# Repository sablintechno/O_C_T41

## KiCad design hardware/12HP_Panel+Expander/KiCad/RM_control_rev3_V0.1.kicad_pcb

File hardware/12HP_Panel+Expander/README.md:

<h1>Front PCB</h1>

<h1>Front</h1>

<h1>Side</h1>

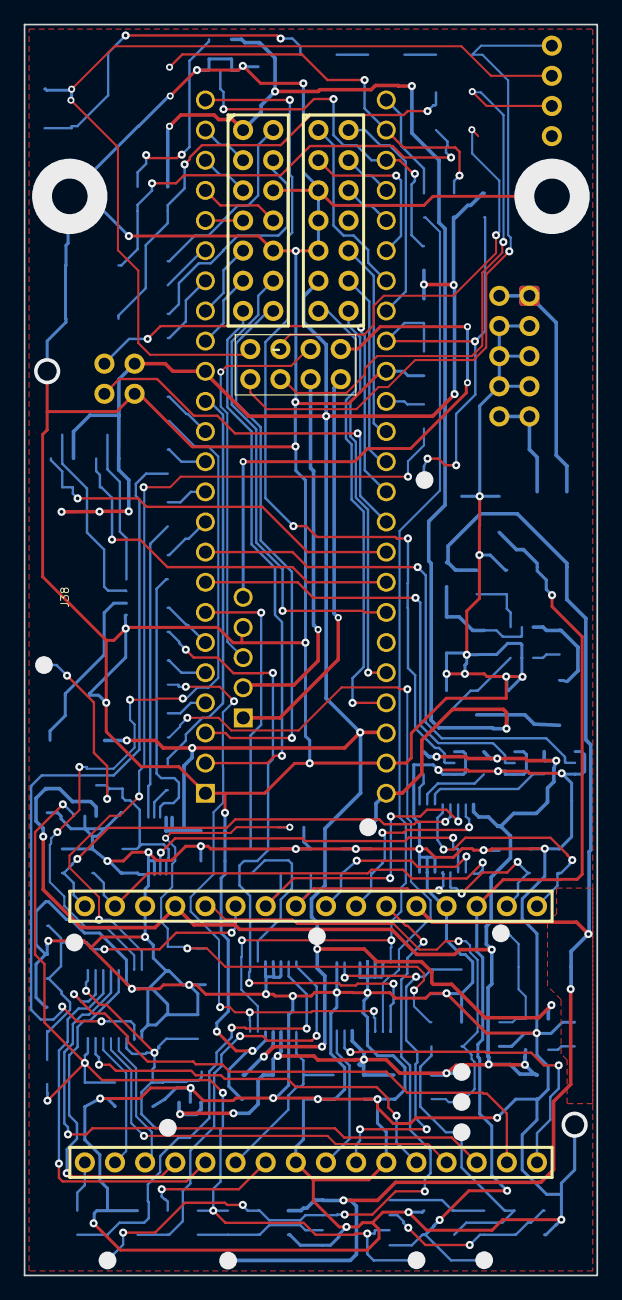
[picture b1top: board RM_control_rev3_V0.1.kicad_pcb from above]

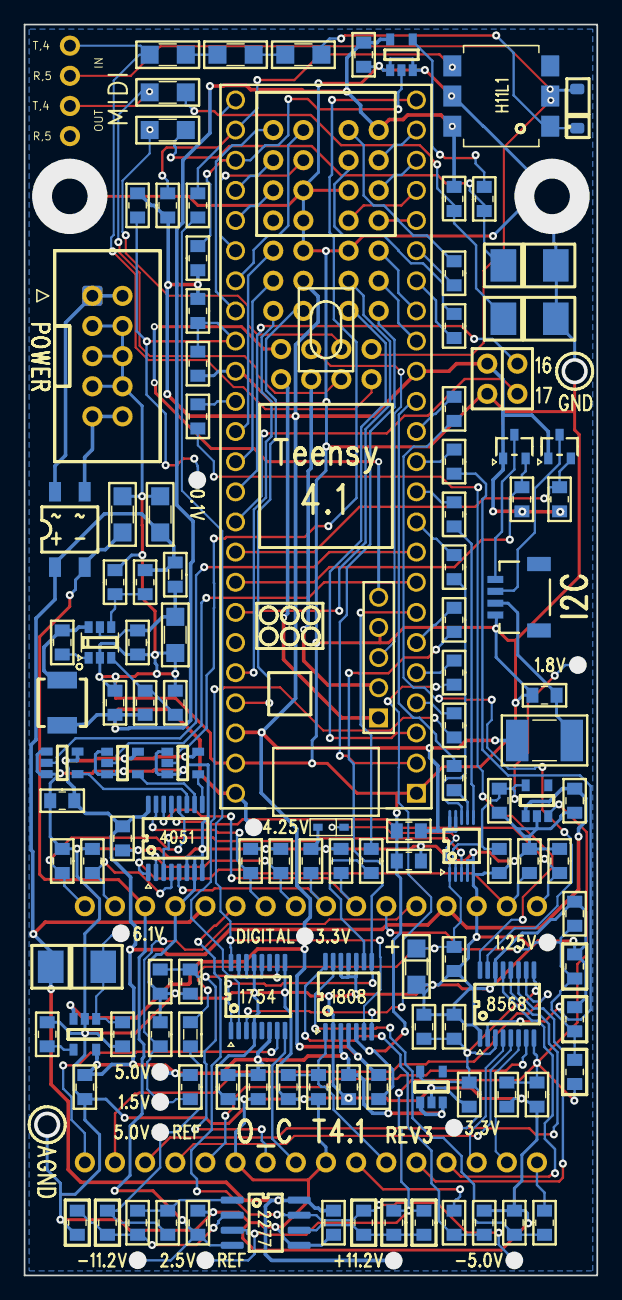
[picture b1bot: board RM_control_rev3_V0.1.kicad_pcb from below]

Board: 2 copper layers, 48.3 x 105.4 mm, 128 parts (2 on the bottom side), 126 nets.

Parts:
C52, C54, C57, C60, C61, C71, C73, C74, C81, C82, C83, C84, C85, C86, C87, C88, C89, C90, C91, C92: C_0805_2012METRIC_PAD1.18X1.45MM_HANDSOLDER_RECTP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; C_0805_2012Metric_Pad1.18x1.45mm_HandSolder_rectpads
C53, C55, C56, C58, C59, C62, C63, C64, C65, C66, C67, C68, C69, C70, C72, C75, C76, C77, C78, C79, C80, C94: C_0805_2012METRIC_PAD1.18X1.45MM_HANDSOLDER_RECTP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; C_0805_2012Metric_Pad1.18x1.45mm_HandSolder_rectpads_C53
C93, C97: C_1206_3216METRIC_PAD1.33X1.80MM_HANDSOLDER_RECTP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; C_1206_3216Metric_Pad1.33x1.80mm_HandSolder_rectpads
C95, C96: C_1206_3216METRIC_PAD1.33X1.80MM_HANDSOLDER_RECTP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; C_1206_3216Metric_Pad1.33x1.80mm_HandSolder_rectpads_C95
D1: DIODE_BRIDGE_REDUCED; Diode_Bridge_reduced
D2, D3, D4: D_SMB_HANDSOLDERING_RECTPADS; D_SMB_Handsoldering_rectpads
D5: D_SOD-123
D6: D_SOD-323F_RECTPADS; D_SOD-323F_rectpads
F1: FUSE_1812_4532METRIC_PAD1.30X3.40MM_HANDSOLDER_RE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; Fuse_1812_4532Metric_Pad1.30x3.40mm_HandSolder_rectpads
J1: PINSOCKET_1X04_P2.54MM_VERTICAL_REDUCED; PinSocket_1x04_P2.54mm_Vertical_reduced
J28, J29: PINSOCKET_2X07_P2.54MM_VERTICAL_REDUCED; PinSocket_2x07_P2.54mm_Vertical_reduced
J30, J31: PINSOCKET_1X16_P2.54MM_VERTICAL_REDUCED; PinSocket_1x16_P2.54mm_Vertical_reduced
J32: IDC-HEADER_2X05_P2.54MM_VERTICAL_REDUCED; IDC-Header_2x05_P2.54mm_Vertical_reduced
J33: PINSOCKET_2X04_P2.54MM_VERTICAL_REDUCED; PinSocket_2x04_P2.54mm_Vertical_reduced
J34: PINHEADER_2X02_P2.54MM_VERTICAL_SYMMETRIC; PinHeader_2x02_P2.54mm_Vertical_symmetric
J38: JST_SMD_1.0MM-4; JST_SMD_1.0mm-4
L1: L_0805_2012METRIC_RECTPADS; L_0805_2012Metric_rectpads
L2: L_ABRACON_ASPI-4030S_RECTPADS; L_Abracon_ASPI-4030S_rectpads
L3: L_0805_2012METRIC_RECTPADS; L_0805_2012Metric_rectpads_L3
Q1, Q2: SOT-23-3_RECTPADS; SOT-23-3_rectpads
R103, R104, R112, R119, R120, R122, R123, R124, R126, R127, R128, R131, R132, R133, R134, R136, R137, R138, R144, R200: R_0805_2012METRIC_PAD1.20X1.40MM_HANDSOLDER_RECTP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; R_0805_2012Metric_Pad1.20x1.40mm_HandSolder_rectpads
R105, R106, R107, R108, R109, R110, R111, R113, R114, R115, R116, R117, R118, R121, R125, R129, R130, R135, R201, R202: R_0805_2012METRIC_PAD1.20X1.40MM_HANDSOLDER_RECTP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; R_0805_2012Metric_Pad1.20x1.40mm_HandSolder_rectpads_R105
R139, R140, R141, R142, R143: R_1206_3216METRIC_PAD1.30X1.75MM_HANDSOLDER_RECTP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; R_1206_3216Metric_Pad1.30x1.75mm_HandSolder_rectpads
U12: TEENSY41; Teensy41
U13: SOT-23-6_RECTPADS; SOT-23-6_rectpads
U14: SOT-23-5_REDUCEDPADS; SOT-23-5_reducedpads
U15, U16, U20, U21, U22, U23: SOT-23-5_REDUCEDPADS; SOT-23-5_reducedpads_U15
U17: MSOP-10_3X3MM_P0.5MM_SILKSCREEN+FOOTPRINT; MSOP-10_3x3mm_P0.5mm_silkscreen+footprint
U18, U19, U25: TSSOP-16_4.4X5MM_P0.65MM_SILKSCREEN; TSSOP-16_4.4x5mm_P0.65mm_silkscreen
U24: TSSOP-14_4.4X5MM_P0.65MM_SILKSCREEN; TSSOP-14_4.4x5mm_P0.65mm_silkscreen
U26: SOIC-8_3.9X4.9MM_P1.27MM_SHIFTEDPADS; SOIC-8_3.9x4.9mm_P1.27mm_shiftedpads
U27: OPTOCOUPLER_H11F3SR2M

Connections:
+3v3: C57.1, C63.1, F1.2, J28.12, J34.1, Q1.1, Q2.1, R119.1, R120.1, R122.1, R123.1, R130.1, R202.1, U12.3.3V, U12.3.3V@, U14.3, U17.9, U17.10, U24.4
+4v: C74.1, C94.1, J29.2, L2.2, R116.1, R127.1, U12.VIN, U23.5, U27.6
+5va: C54.1, C55.1, C64.1, C66.1, C70.1, C72.1, C76.1, J30.4, R125.1, U14.5, U15.1, U15.3, U16.1, U18.16, U20.5, U21.5, U22.5, U24.3, U25.6
+12va: C67.1, C95.1, D1.1, D2.1, J30.12, L1.1, R129.1, U26.8
-12va: C68.2, C96.1, D1.2, J30.14, U26.4
/adc_cs: R107.1, U12.9
/adc_miso: R112.2, U12.12
/adc_mux_a0: U12.7, U20.2
/adc_mux_a1: U12.6, U21.2
/adc_mux_a2: U12.32, U22.2
/adc_sck: R108.1, U12.8
/dac_cs: R106.1, U12.10
/dac_mosi: R105.1, U12.11
/dac_sck: R114.1, U12.13
/debug1: J34.2, U12.16
/debug2: J34.4, U12.17
/enc_l_a: J29.4, U12.31
/enc_l_b: J29.6, U12.30
/enc_l_sw: J29.12, U12.24
/enc_r_a: J28.5, U12.37
/enc_r_b: J28.3, U12.36
/enc_r_sw: J29.10, U12.25
/hw_id: R121.1, R130.2, R202.2, U12.41
/i2c_scl: Q1.2, R122.2, U12.19
/i2c_sda: Q2.2, R123.2, U12.18
/i2s_bclk: R109.1, U12.4
/i2s_data_adc: R113.1, U12.5
/i2s_data_dac: R111.1, U12.2
/i2s_lrclk: R110.1, U12.3
/i2s_mclk: R115.1, U12.33
/midi_in: R119.2, U12.34, U27.4
/midi_out: R120.2, U12.35, U23.2
/oled_cs: J28.1, U12.40
/oled_dc: J28.2, U12.39
/oled_mosi: R104.1, U12.26
/oled_rst: J28.4, U12.38
/oled_sck: R103.1, U12.27
/sw_a: J29.7, U12.29
/sw_b: J28.9, U12.14
/sw_x: J29.8, U12.28
/sw_y: J28.11, U12.15
/sw_zap: J29.11, U12.20
/tr1: J29.14, U12.0
/tr2: J29.13, U12.1
/tr3: J28.14, U12.23
/tr4: J28.13, U12.22
D+_B: J33.6, U12.D+
D-_B: J33.5, U12.D-
SHLD_B: J33.8, U12.GND@_3
VBUS_B: J33.7, U12.+5V
earth: C53.2, C57.2, C63.2, C73.2, C74.2, C94.2, C95.2, C96.2, C97.2, D3.2, D4.2, J28.6, J28.8, J28.10, J29.5, J29.9, J32.3, J32.4, J32.5, J32.6, J32.7, J32.8, J34.3, J38.1, R121.2, R126.2, R128.2, R144.1, U12.GND, U12.GND@, U12.GND@_1, U12.GND@_2, U13.2, U23.1, U23.3, U24.5, U27.5
gnd: C54.2, C55.2, C56.2, C58.2, C59.2, C60.2, C61.2, C62.2, C64.2, C65.2, C66.2, C67.2, C68.1, C69.2, C70.2, C71.2, C72.2, C75.2, C76.2, C77.2, C78.2, C79.2, C80.2, C81.2, C82.2, C83.2, C84.2, C85.2, C86.2, C87.2, C88.2, C89.2, C90.2, C91.2, C93.2, D6.2, J30.3, J30.13, J31.8, J31.11, R124.2, R133.2, R136.1, R144.2, R200.2, U14.2, U15.2, U16.2, U17.4, U17.5, U18.6, U18.7, U18.8, U19.1, U19.14, U20.1, U20.3, U21.1, U21.3, U22.1, U22.3, U24.2, U24.10, U24.11, U24.12, U25.4, U25.9, U25.12, U25.13, U25.14, U25.15, U26.5
net-(c92-pad2): C92.2, R118.1, U26.1
net-(d2-a): C69.1, D2.2, U14.1
net-(d3-k): D3.1, R117.2, R140.1
net-(d4-k): D4.1, R116.2, R139.1
net-(d5-a): D5.2, J1.2, J33.2, U27.2
net-(d5-k): D5.1, R141.1, U27.1
net-(d6-k): C59.1, C93.1, D6.1, L3.2, U17.1
net-(j29-pin_1): J29.1, R103.2
net-(j29-pin_3): J29.3, R104.2
net-(j30-pin_1): C88.1, J30.1, U18.13
net-(j30-pin_2): C87.1, J30.2, U18.1
net-(j30-pin_5): J30.5, R124.1, R125.2
net-(j30-pin_6): C61.1, J30.6, R133.1, R134.2, R200.1
net-(j30-pin_7): C86.1, J30.7, U18.14
net-(j30-pin_8): C85.1, J30.8, U18.5
net-(j30-pin_9): C84.1, J30.9, U18.2
net-(j30-pin_10): C83.1, J30.10, U18.15
net-(j30-pin_11): J30.11, R138.2, U26.7
net-(j30-pin_15): C82.1, J30.15, U18.4
net-(j30-pin_16): C81.1, J30.16, U18.12
net-(j31-pin_1): J31.1, R132.2
net-(j31-pin_2): J31.2, U19.6
net-(j31-pin_3): J31.3, U19.4
net-(j31-pin_4): J31.4, U19.13
net-(j31-pin_5): J31.5, U19.11
net-(j31-pin_6): C65.1, C77.1, J31.6, U24.1
net-(j31-pin_7): J31.7, R131.2
net-(j31-pin_9): J31.9, U25.8
net-(j31-pin_10): C56.1, C75.1, J31.10, U25.10
net-(j31-pin_12): J31.12, U19.7
net-(j31-pin_13): J31.13, U19.5
net-(j31-pin_14): J31.14, U19.12
net-(j31-pin_15): J31.15, U19.10
net-(j31-pin_16): J31.16, U25.7
net-(j32-pin_1): D1.3, J32.1, J32.2
net-(j32-pin_10): D1.4, J32.9, J32.10
net-(j33-pin_1): J1.1, J33.1, R143.2
net-(j33-pin_3): J1.3, J33.3, R139.2
net-(j33-pin_4): J1.4, J33.4, R140.2
net-(j38-pin_2): C73.1, F1.1, J38.2
net-(j38-pin_3): J38.3, Q2.3
net-(j38-pin_4): J38.4, Q1.3
net-(l3-pad1): L3.1, R118.2, R137.2
net-(r141-pad2): R141.2, R142.1
net-(r142-pad2): R142.2, R143.1
net-(u13-cb): C52.1, U13.1
net-(u13-en): R128.1, R129.2, U13.4
net-(u13-fb): R126.1, R127.2, U13.3
net-(u13-sw): C52.2, L2.1, U13.6
net-(u13-vin): C53.1, C97.1, L1.2, U13.5
net-(u14-bp): C91.1, U14.4
net-(u15-out): C60.1, C71.1, C78.1, U15.5, U19.3, U19.9
net-(u16-en): C62.1, C79.1, R134.1, R135.1, R201.1, U16.3, U19.8, U26.3
net-(u16-out): C58.1, C80.1, U16.5, U17.2
net-(u17-ain+): U17.3, U18.3
net-(u17-cnvst): R107.2, U17.6
net-(u17-sclk): R108.2, U17.8
net-(u17-sdo): R112.1, U17.7
net-(u18-s0): U18.11, U20.4
net-(u18-s1): U18.10, U21.4
net-(u18-s2): U18.9, U22.4
net-(u19-din): R105.2, U19.15
net-(u19-sclk): R114.2, U19.16
net-(u19-~sync): R106.2, U19.2
net-(u23-y): R117.1, U23.4
net-(u24-bck): R109.2, U24.8, U25.1
net-(u24-dout): R113.2, U24.9
net-(u24-lrck): R110.2, U24.7, U25.3
net-(u24-scki): R115.2, U24.6, U25.16
net-(u24-vinl): C90.1, R132.1, U24.13
net-(u24-vinr): C89.1, R131.1, U24.14
net-(u25-data): R111.2, U25.2
net-(u26a--): C92.1, R136.2, R137.1, U26.2
net-(u26b--): R135.2, R138.1, R201.2, U26.6

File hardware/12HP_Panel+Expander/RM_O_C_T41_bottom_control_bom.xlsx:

Comment | Designator | Footprint | LCSC Part # |  |  | Original Part
22pF | C92 | 0805 | C1804 | CL21C220JBANNNC | C105623 | CC0805JRNPO9BN220
 | C81, C82, C83, C84, C85, C86, C87, C88, C89, C90 | 0805 | C1835 | 0805CG681J500NT | C107121 | CC0805JRNPO9BN681
10nF | C91 | 0805 | C24666 | 0805B103J500NT | C58456 | CC0805JRX7R9BB103
1.0uF | C69, C70, C71, C72, C73 | 0805 | C541528 | CC0805JKX7R9BB105 | C541528 | CC0805JKX7R9BB105
0.1uF | C52, C53, C54, C55, C56, C57, C58, C59, C60, C61, C62, C63, C64, C65, C66, C67,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 | 0805 | C29926 | 0805B104J500NT | C111492 | CC0805JRX7R9BB104
10uF | C74, C75, C76, C77, C78, C79, C80 | 0805 | C15850 | CL21A106KAYNNNE | C307520 | CL21A106KOQNNNG
10uF | C93 | 1206 | C7171 | TAJA106K016RNJ | C7171 | TAJA106K016RNJ
22uF | C95, C96, C97 | 1206 | C12891 | CL31A226KAHNNNE | C12891 | CL31A226KAHNNNE
Bridge Rectifier | D1 | TO-269AA | C52151 | HD01-T | C52151 | HD01-T
Diode Zener | D2, D3, D4 |  | C142361 | 1SMB5918BT3G | C142361 | 1SMB5918BT3G
Diode | D5 | SDO123 | C77978 | 1N4148W-TP | C77978 | 1N4148W-TP
Diode | D6 | SDO123 |  |  |  | BZT52B5V1S | mod 5V
PTC Fuse | F1 | 1812 | C12430 | MF-MSMF010-2 | C12430 | MF-MSMF010-2
Ferrite Bead | L1 | 0805 | C2441364 | HZ0805E601R-10 | C2441364 | HZ0805E601R-10
Inductor | L2 |  | C2921170 | BCIHP0420SC-100M | C2921170 | BCIHP0420SC-100M | LQH44NN100K03L | LQH44PH100MPRL | CY43-10UH | MDA4020-100M | IFSC1515AHER100M01
Inductor | L3 | 0805 | C223145 | BRC2012T1R5MD | C223145 | BRC2012T1R5MD
Mosfet | Q1, Q2 | SOT23 | C80498 | FDV303N | C80498 | FDV303N
0 | R144 | 0805 | C17477 | 0805W8F0000T5E | C17477 | 0805W8F0000T5E
75 | R141, R142, R143 | 1206 | C17987 | 1206W4F750JT5E | C4185489 | CRCW120675R0FKEAC
120 | R139, R140 | 1206 |  |  |  |  | mod 5V
100 | R103, R104, R105, R106, R107, R108, R109, R110, R111, R112, R113, R114, R115, R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 | 0805 | C17408 | 0805W8F1000T5E | C105577 | RC0805FR-07100RL
220 | R118 | 0805 | C17557 | 0805W8F2200T5E | C114519 | RC0805FR-07220RL
470 | R119 | 0805 | C17710 | 0805W8F4700T5E | C114564 | RC0805FR-07470RL
1K | R131, R132 | 0603 | C21190 | 0603WAF1001T5E | C22548 | RC0603FR-071KL
5.11K 1% | R126 | 0805 | C46039 | 0805W8F5111T5E | C276311 | RC0805FR-075K11L
10K 0,005% | R133, R134, R135, R136, R137 | 0805 | C706400 | RT0805WRD0710KL | C2073470 | ERA-6ARW103V
4k7 | R133 | 0805 |  |  |  |  | mod DAC
5k8 | R134 | 0805 |  |  |  |  | mod DAC
4.7K 1% | R121, R123, R124, R120, R122 | 0805 | C17673 | 0805W8F4701T5E | C60816 | RC0805FR-074K7L
11K | R125 | 0805 | C17429 | 0805W8F1102T5E | C137597 | RC0805FR-0711KL
20K 0,05% | R138 | 0805 | C706402 | RT0805WRD0720KL | C4141407 | ERA-6ARW203V | AR05ATB2002 | PTFR0805Q20K0N9
22K | R128 | 0805 | C17560 | 0805W8F2202T5E | C114565 | RC0805FR-0722KL
27k | R127 | 0805 |  |  |  |  | mod 5V
150K 1% | R129 | 0805 | C17470 | 0805W8F1503T5E | C114558 | RC0805FR-07150KL
100K 1% | R130 | 0805 |  |  |  |  | mod HW
DNP | R200, R201, R202
Buck Converter | U13 | SOT-23-6 | C3193129 | LMR54406FDBVR | C3193129 | LMR54406FDBVR
LDO 5V | U14 | SOT-23-5 | C37560592 | LP2985A-50DBVRM3 | C37560592 | LP2985A-50DBVRM3 | LP2985-50DBVR
LDO 3.3V | U15 | SOT-23-5 | C2862740 | TPS7A2033PDBVR | C2862740 | TPS7A2033PDBVR
LDO 1.8V | U16 | SOT-23-5 | C92498 | LP5907MFX-1.8/NOPB | C92498 | LP5907MFX-1.8/NOPB
ADC | U17 | MSOP-10 | C635977 | MCP33131D-05-E/MS | C635977 | MCP33131D-05-E/MS
analog mux | U18 | TSSOP-16 | C547982 | 74LV4051PW,118 | C547982 | 74LV4051PW,118
DAC | U19 | TSSOP-16 | C2680013 | DAC8568IBPWR | C2680013 | DAC8568IBPWR
Buffer level shifter | U20, U21, U22, U23 | SOT-23-5 | C473338 | SN74LV1T125DBVR | C473338 | SN74LV1T125DBVR
Audio ADC | U24 | TSSOP-14 | C55513 | PCM1808PWR | C55513 | PCM1808PWR
Audio DAC | U25 | SSOP-16-150mil | C294211 | PCM1754DBQR | C294211 | PCM1754DBQR
Dual Opamp | U26 | SOIC-8 | C962986 | OPA2277UA | C962986 | OPA2277UA
Optocoupler | U27 | DIP6 | C78588 | H11L1 | C78588 | H11L1 | H11L1SVM
J38 | 1 | Connector, JST 4 pin, Sparkfun QWIIC |  |  |  | PRT-14417
J28-J29 | 2 | Socket, 7x2 (omit if soldering boards together) |  |  |  | TSW-107-06-T-S
J30-J31 | 2 | Socket, 16x1 (omit if soldering boards together) |  |  |  | TSW-116-06-T-S
J32 | 1 | Header, 5x2 Shrouded |  |  |  | 68015-405HLF
J33 | 1 | Header, 4x1 |  |  |  | 68000-204HLF
J34-J35 | 2 | Header, 2x1 (omit if debug signals not needed)
J36-J37 | 2 | Test Point (omit if not needed) Keystone 5011
U12 | 1 | Teensy 4.1 (with headers and sockets) |  |  |  | 16996

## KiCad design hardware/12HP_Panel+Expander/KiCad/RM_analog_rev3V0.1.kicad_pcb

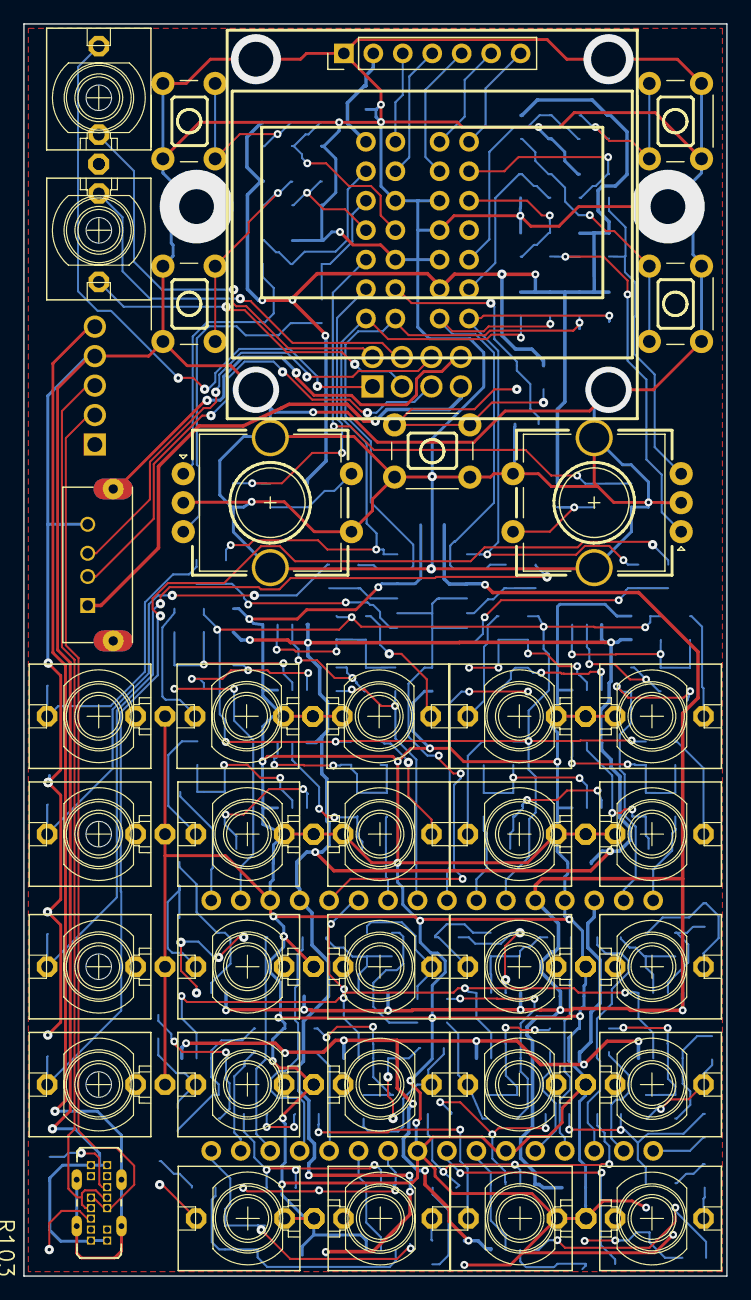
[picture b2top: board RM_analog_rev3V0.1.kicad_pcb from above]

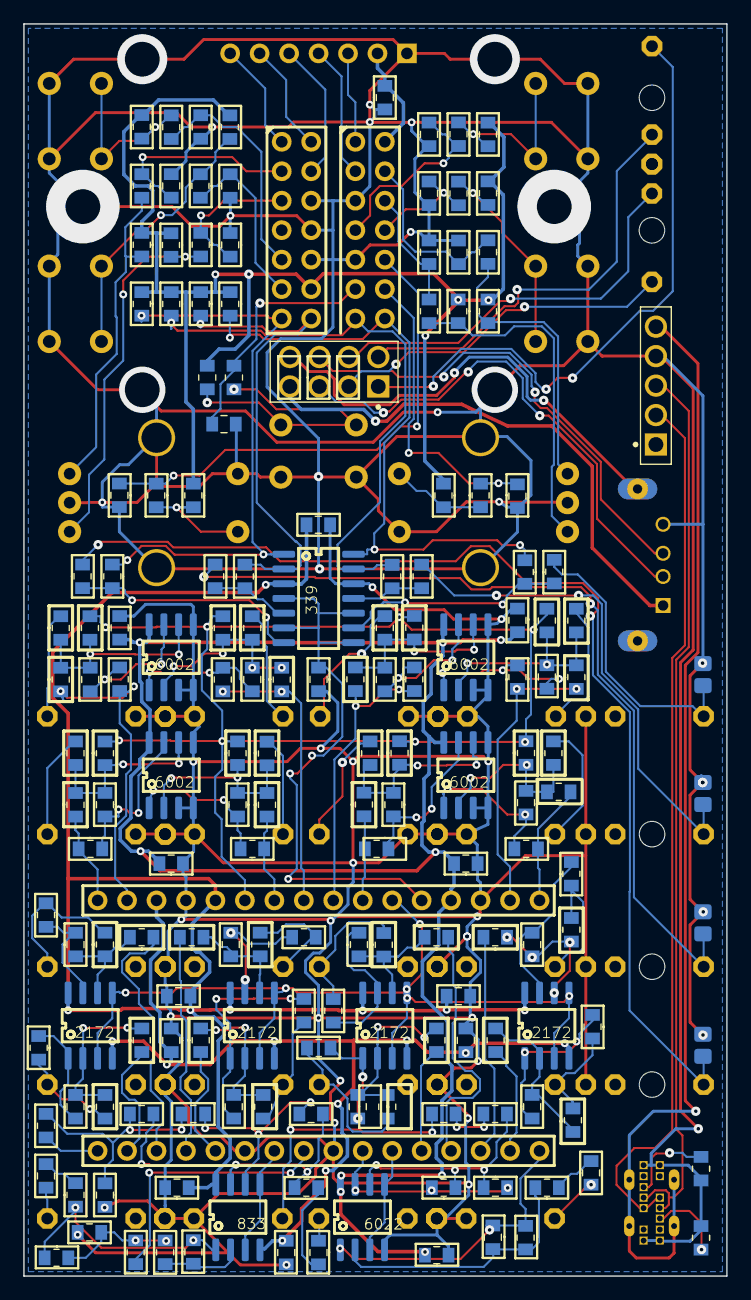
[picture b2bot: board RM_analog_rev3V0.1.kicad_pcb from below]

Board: 2 copper layers, 60.6 x 108.0 mm, 212 parts (6 on the bottom side), 148 nets.

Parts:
C1, C2, C3, C4, C5, C11, C12, C26, C28, C30, C34, C35, C36, C37, C48, C50: C_0805_2012METRIC_PAD1.18X1.45MM_HANDSOLDER_RECTP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; C_0805_2012Metric_Pad1.18x1.45mm_HandSolder_rectpads
C6, C7, C8, C9, C10, C13, C14, C15, C16, C17, C18, C19, C20, C21, C22, C23, C24, C25, C27, C29, C31, C32, C33, C38, C39, C40, C41, C42, C43, C44, C45, C46, C47, C49, C51: C_0805_2012METRIC_PAD1.18X1.45MM_HANDSOLDER_RECTP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; C_0805_2012Metric_Pad1.18x1.45mm_HandSolder_rectpads_C6
J1: DEV_J1; P51
J2: DEV_J2; P51
J3: DEV_J3; P51
J4, J8: JACK O_C; Jack_O_C
J5: DEV_J5; P51
J6: DEV_J6; P51
J7: DEV_J7; P51
J9: DEV_J9; P51
J10: DEV_J10; P51
J11: DEV_J11; P51
J12: DEV_J12; P51
J13: DEV_J13; P51
J14: DEV_J14; P51
J15: DEV_J15; P51
J16: DEV_J16; P51
J17: DEV_J17; P51
J18: DEV_J18; P51
J19: DEV_J19; P51
J20: DEV_J20; P51
J21: PINHEADER_1X07_P2.54MM_VERTICAL; PinHeader_1x07_P2.54mm_Vertical
J22, J23: PINHEADER_2X07_P2.54MM_VERTICAL_REDUCED; PinHeader_2x07_P2.54mm_Vertical_reduced
J24: RHDRV8W80P254_4X2_1066X508H865_AP1
J25: RHDRV5W80P254_5X1_1320X250H875_AP1
J26, J27: PINHEADER_1X16_P2.54MM_VERTICAL_REDUCED; PinHeader_1x16_P2.54mm_Vertical_reduced
MIDI_IN0: DEV_MIDI_IN; P78
MIDI_OUT0: DEV_MIDI_OUT; P78
R1, R2, R3, R4, R5, R10, R11, R12, R13, R14, R15, R16, R23, R24, R25, R26, R27, R28, R29, R30, R35, R36, R37, R38, R39, R40, R41, R42, R51, R52, R53, R54, R55, R56, R57, R58, R59, R60, R61, R62, R79, R80, R81, R82, R83, R87, R89, R90, R101: R_0805_2012METRIC_PAD1.20X1.40MM_HANDSOLDER_RECTP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; R_0805_2012Metric_Pad1.20x1.40mm_HandSolder_rectpads
R6, R7, R8, R9, R17, R18, R19, R20, R21, R22, R31, R32, R33, R34, R43, R44, R45, R46, R47, R48, R49, R50, R63, R64, R65, R66, R67, R68, R69, R70, R71, R72, R73, R74, R75, R76, R77, R78, R84, R85, R86, R88, R91, R92, R93, R94, R95, R96, R97, R98, R99, R100, R102: R_0805_2012METRIC_PAD1.20X1.40MM_HANDSOLDER_RECTP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; R_0805_2012Metric_Pad1.20x1.40mm_HandSolder_rectpads_R6
R103: 4k7; R_0805_2012Metric_Pad1.20x1.40mm_HandSolder_rectpads_R103
R104: 4k7; R_0805_2012Metric_Pad1.20x1.40mm_HandSolder_rectpads_R104
R105, R106, R107, R108: 100K; RES_0805
SW1, SW2, SW3, SW4, SW5: SW_PUSH_6MM; SW_PUSH_6mm
SW6, SW7: ROTARYENCODER_ALPS_EC11E-SWITCH_VERTICAL_H20MM_CI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; RotaryEncoder_Alps_EC11E-Switch_Vertical_H20mm_CircularMoun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
TR1: DEV_TR1; P51
TR2: DEV_TR2; P78
TR3: DEV_TR3; P78
TR4: DEV_TR4; P78
U1: SOIC-14_3.9X8.7MM_P1.27MM_SHIFTEDPADS; SOIC-14_3.9x8.7mm_P1.27mm_shiftedpads
U2, U3, U4, U5, U6, U7, U8, U9, U10, U11: SOIC-8_3.9X4.9MM_P1.27MM_SHIFTEDPADS; SOIC-8_3.9x4.9mm_P1.27mm_shiftedpads
USB_A0: USB_A_ALIEXPRESS_VERTICAL; USB_A_AliExpress_Vertical
USB_C0: SPARKFUN USB-C VERTICAL; SparkFun_USB-C_Vertical

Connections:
+3v3: J23.12, R1.1, R2.1, R3.1, R4.1, R5.1, R11.1, R12.1, R13.1, R14.1, R15.1, R16.1, R23.1, R24.1, R25.1, R26.1
+5va: C14.1, C15.1, C16.1, C17.1, C31.1, J26.4, U2.8, U3.8, U4.8, U5.8, U10.8
+12va: C13.1, C27.1, C29.1, C32.1, J26.12, U1.3, U6.8, U7.8, U8.8, U9.8, U11.8
-12va: C28.2, C30.2, C33.2, J26.14, U6.4, U7.4, U8.4, U9.4, U11.4
/audio_in_l: C46.1, J27.1, R101.2, U10.1
/audio_in_r: C47.1, J27.7, R102.2, U10.7
/audio_out_l: J27.16, R93.1
/audio_out_r: J27.9, R94.1
/bias: J26.6, U6.3, U6.5, U7.3, U7.5, U8.3, U8.5, U9.3, U9.5
/clk: J21.3, J22.1
/cs: J21.7, J23.1
/cv1: J26.2, R51.2, R59.2
/cv2: J26.8, R52.2, R60.2
/cv3: J26.9, R53.2, R61.2
/cv4: J26.15, R54.2, R62.2
/cv5: J26.1, R55.2, R63.2
/cv6: J26.7, R56.2, R64.2
/cv7: J26.10, R57.2, R65.2
/cv8: J26.16, R58.2, R66.2
/cv_a: J27.3, R67.1
/cv_b: J27.4, R68.1
/cv_c: J27.13, R69.1
/cv_d: J27.14, R70.1
/cv_e: J27.2, R71.1
/cv_f: J27.5, R72.1
/cv_g: J27.12, R73.1
/cv_h: J27.15, R74.1
/dac_a: J9.T, R75.2, R83.2
/dac_b: J10.T, R76.2, R84.2
/dac_c: J11.T, R77.2, R85.2
/dac_d: J12.T, R78.2, R86.2
/dac_e: J13.T, R79.2, R87.2
/dac_f: J14.T, R80.2, R88.2
/dac_g: J15.T, R81.2, R89.2
/dac_h: J16.T, R82.2, R90.2
/dc: J21.6, J23.2
/offset: J26.11, R43.2, R44.2, R45.2, R46.2, R47.2, R48.2, R49.2, R50.2
/res: J21.5, J23.4
/sda: J21.4, J22.3
/thres: C26.1, J26.5, U1.4, U1.6, U1.8, U1.10
/tr1: J22.14, R23.2, R31.2, U1.14
/tr2: J22.13, R24.2, R32.2, U1.13
/tr3: J23.14, R25.2, R33.2, U1.2
/tr4: J23.13, R26.2, R34.2, U1.1
/vcc: C1.1, J21.2, J22.2
D+_B: J24.6, USB_A0.3
D+_C: J25.3, USB_C0.A6, USB_C0.B6
D-_B: J24.5, USB_A0.2
D-_C: J25.2, USB_C0.A7, USB_C0.B7
Net_141: R103.2, USB_C0.B5
Net_142: R104.1, USB_C0.A5
SHLD: J25.5, USB_C0.S1, USB_C0.S1@, USB_C0.S1@_1, USB_C0.S1@_2
SHLD_B: J24.8, USB_A0.5, USB_A0.5@
VBUS_B: J24.7, USB_A0.1
earth: C1.2, C2.2, C3.2, C4.2, C5.2, C6.2, C7.2, C8.2, C9.2, C10.2, C11.2, C12.2, J21.1, J22.5, J22.9, J23.6, J23.8, J23.10, J25.4, R103.1, R104.2, R105.2, R106.2, R107.2, R108.2, SW1.1, SW1.1@, SW2.1, SW2.1@, SW3.1, SW3.1@, SW4.1, SW4.1@, SW5.1, SW5.1@, SW6.C, SW6.MP, SW6.MP@, SW6.S2, SW7.C, SW7.MP, SW7.MP@, SW7.S2, USB_A0.4, USB_C0.A1, USB_C0.A12, USB_C0.B1, USB_C0.B12
gnd: C13.2, C14.2, C15.2, C16.2, C17.2, C26.2, C27.2, C28.1, C29.2, C30.1, C31.2, C32.2, C33.1, C42.1, C43.1, J1.S, J1.TN, J2.S, J2.TN, J3.S, J3.TN, J4.S, J4.TN, J5.S, J5.TN, J6.S, J6.TN, J7.S, J7.TN, J8.S, J8.TN, J9.S, J10.S, J11.S, J12.S, J13.S, J14.S, J15.S, J16.S, J17.S, J17.TN, J18.S, J19.S, J19.TN, J20.S, J26.3, J26.13, J27.8, J27.11, TR1.S, TR2.S, TR3.S, TR4.S, U1.12, U2.3, U2.4, U2.5, U3.3, U3.4, U3.5, U4.3, U4.4, U4.5, U5.3, U5.4, U5.5, U10.4
net-(c18-pad1): C18.1, R59.1, U2.1
net-(c19-pad1): C19.1, R60.1, U2.7
net-(c20-pad1): C20.1, R61.1, U3.1
net-(c21-pad1): C21.1, R62.1, U3.7
net-(c22-pad1): C22.1, R63.1, U4.1
net-(c23-pad1): C23.1, R64.1, U4.7
net-(c24-pad1): C24.1, R65.1, U5.1
net-(c25-pad1): C25.1, R66.1, U5.7
net-(c34-pad1): C34.1, R83.1, U6.7
net-(c35-pad1): C35.1, R84.1, U7.7
net-(c36-pad1): C36.1, R85.1, U8.7
net-(c37-pad1): C37.1, R86.1, U9.7
net-(c38-pad1): C38.1, R87.1, U6.1
net-(c39-pad1): C39.1, R88.1, U7.1
net-(c40-pad1): C40.1, R89.1, U8.1
net-(c41-pad1): C41.1, R90.1, U9.1
net-(c42-pad2): C42.2, R93.2, R95.1, R97.2
net-(c43-pad2): C43.2, R94.2, R96.1, R98.2
net-(c44-pad2): C44.2, R91.1, R97.1, U11.7
net-(c45-pad2): C45.2, R92.1, R98.1, U11.1
net-(c48-pad1): C48.1, J18.T
net-(c48-pad2): C48.2, R91.2
net-(c49-pad1): C49.1, J20.T
net-(c49-pad2): C49.2, R92.2
net-(c50-pad1): C50.1, R99.1
net-(c50-pad2): C50.2, J17.T
net-(c51-pad1): C51.1, R100.1
net-(c51-pad2): C51.2, J19.T
net-(d5-a): J24.2, MIDI_IN0.TN
net-(j5-padt): J5.T, R39.1
net-(j6-padt): J6.T, R40.1
net-(j7-padt): J7.T, R41.1
net-(j8-padt): J8.T, R42.1
net-(j22-pin_4): C7.1, J22.4, R17.2
net-(j22-pin_6): C8.1, J22.6, R18.2
net-(j22-pin_7): C2.1, J22.7, R6.1
net-(j22-pin_8): C3.1, J22.8, R7.1
net-(j22-pin_10): C12.1, J22.10, R22.2
net-(j22-pin_11): C6.1, J22.11, R10.1
net-(j22-pin_12): C11.1, J22.12, R21.2
net-(j23-pin_3): C10.1, J23.3, R20.2
net-(j23-pin_5): C9.1, J23.5, R19.2
net-(j23-pin_9): C4.1, J23.9, R8.1
net-(j23-pin_11): C5.1, J23.11, R9.1
net-(j24-pin_1): R27.1, R105.1, TR1.T
net-(j24-pin_3): R28.1, R108.1, TR2.T
net-(j25-pin_1): R29.1, R106.1, TR3.T
net-(j25-pin_3): R30.1, R107.1, TR4.T
net-(j27-pin_6): J27.6, U10.3, U10.5
net-(j27-pin_10): J27.10, U11.3, U11.5
net-(j33-pin_1): J24.1, MIDI_IN0.T
net-(j33-pin_3): J24.3, MIDI_OUT0.T
net-(j33-pin_4): J24.4, MIDI_OUT0.TN
net-(jp1-b): J1.T, R35.1
net-(jp2-b): J2.T, R36.1
net-(jp3-b): J3.T, R37.1
net-(jp4-b): J4.T, R38.1
net-(r1-pad2): R1.2, R6.2, SW1.2, SW1.2@
net-(r2-pad2): R2.2, R7.2, SW2.2, SW2.2@
net-(r3-pad2): R3.2, R8.2, SW3.2, SW3.2@
net-(r4-pad2): R4.2, R9.2, SW4.2, SW4.2@
net-(r10-pad2): R5.2, R10.2, SW5.2, SW5.2@
net-(r11-pad2): R11.2, R17.1, SW6.A
net-(r12-pad2): R12.2, R18.1, SW6.B
net-(r13-pad2): R13.2, R19.1, SW7.A
net-(r14-pad2): R14.2, R20.1, SW7.B
net-(r15-pad2): R15.2, R21.1, SW6.S1
net-(r16-pad2): R16.2, R22.1, SW7.S1
net-(u1a-+): R29.2, R33.1, U1.5
net-(u1b-+): R30.2, R34.1, U1.7
net-(u1c-+): R28.2, R32.1, U1.11
net-(u1d-+): R27.2, R31.1, U1.9
net-(u2a--): C18.2, R35.2, R43.1, R51.1, U2.2
net-(u2b--): C19.2, R36.2, R44.1, R52.1, U2.6
net-(u3a--): C20.2, R37.2, R45.1, R53.1, U3.2
net-(u3b--): C21.2, R38.2, R46.1, R54.1, U3.6
net-(u4a--): C22.2, R39.2, R47.1, R55.1, U4.2
net-(u4b--): C23.2, R40.2, R48.1, R56.1, U4.6
net-(u5a--): C24.2, R41.2, R49.1, R57.1, U5.2
net-(u5b--): C25.2, R42.2, R50.1, R58.1, U5.6
net-(u6a--): C38.2, R71.2, R79.1, U6.2
net-(u6b--): C34.2, R67.2, R75.1, U6.6
net-(u7a--): C39.2, R72.2, R80.1, U7.2
net-(u7b--): C35.2, R68.2, R76.1, U7.6
net-(u8a--): C40.2, R73.2, R81.1, U8.2
net-(u8b--): C36.2, R69.2, R77.1, U8.6
net-(u9a--): C41.2, R74.2, R82.1, U9.2
net-(u9b--): C37.2, R70.2, R78.1, U9.6
net-(u10a--): C46.2, R99.2, R101.1, U10.2
net-(u10b--): C47.2, R100.2, R102.1, U10.6
net-(u11a--): C45.1, R96.2, U11.2
net-(u11b--): C44.1, R95.2, U11.6

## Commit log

2026-05-20 Add Files
2026-06-08 Add BOM & CPL
2026-06-14 Create KiCad
2026-06-14 add kicad files
2026-06-14 del file
